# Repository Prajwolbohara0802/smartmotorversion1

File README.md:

# Smart Motors using Arduino

React to this comment or reply here to show your support on this project.

## Components Needed

[Arduino Nano](https://static-01.daraz.com.np/p/9f4c40402cecd5b19b21ea068286c35f.jpg_720x720.jpg_.webp)

[TFT LCD Screen](https://udvabony.com/wp-content/uploads/2019/04/2.4-inch-tft-lcd-shield-for-arduino.jpg)

## Library Needed

Adafruit_GFX.h
Touchscreen.h
Adafruit_TFTLCD.h

[FZP71N4IT58ZZL4.zip](Smart%20Motors%20using%20Arduino%20c2e0098330564f6db3aee58281a698de/FZP71N4IT58ZZL4.zip)

All of these library can be found in Arduino IDE

| TFT pin  | Arduino Pin |
| --- | --- |
| LCD_RD | A0 |
| LCD_WR | A1 |
| LCD_RS | A2 |
| LCD_CS | A3 |
| LCD_RST (optional) | A4 |
| LCD_D0 |  8 |
| LCD_D1 | 9 |
| LCD_D2 | 2 |
| LCD_D3 | 3 |
| LCD_D4 | 4 |
| LCD_D5 | 5 |
| LCD_D6 | 6 |
| LCD_D7 | 7 |
| GND | GND |
| 3.3v  | 3.3 v |
- [x]  

## Pin that are used

| analog device  | Arduino pin |
| --- | --- |
| Sensor | A5 |
|  |  |
|  |  |
- it’s optional to connect Arduino 5v to 5V pin of TFT screen because TFT can easily powerup with the help of 3.3 V
- I prefer connecting the LCD_RST pin of TFT with the RST pin of the Arduino because it left a option to connect the other analog reading device.
- **5V**: Module power supply – 5 V
- **3**.**3V**: Module power supply – 3.3 V
- **GND**: Ground
- **LCD_RST**: LCD bus reset signal, low level reset
- **LCD_CS**: LCD bus chip select signal, low level enable
- **LCD_RS:** LCD bus command / data selection signal, low level: command, high level: data
- **LCD_WR:** LCD bus write signal
- **LCD_RD:** LCD bus read signal
- **LCD_D0:** LCD 8-bit data Bit0
- **LCD_D1:** LCD 8-bit data Bit1
- **LCD_D2:** LCD 8-bit data Bit2
- **LCD_D3:** LCD 8-bit data Bit3
- **LCD_D4:** LCD 8-bit data Bit4
- **LCD_D5:** LCD 8-bit data Bit5
- **LCD_D6:** LCD 8-bit data Bit6
- **LCD_D7:** LCD 8-bit data Bit7

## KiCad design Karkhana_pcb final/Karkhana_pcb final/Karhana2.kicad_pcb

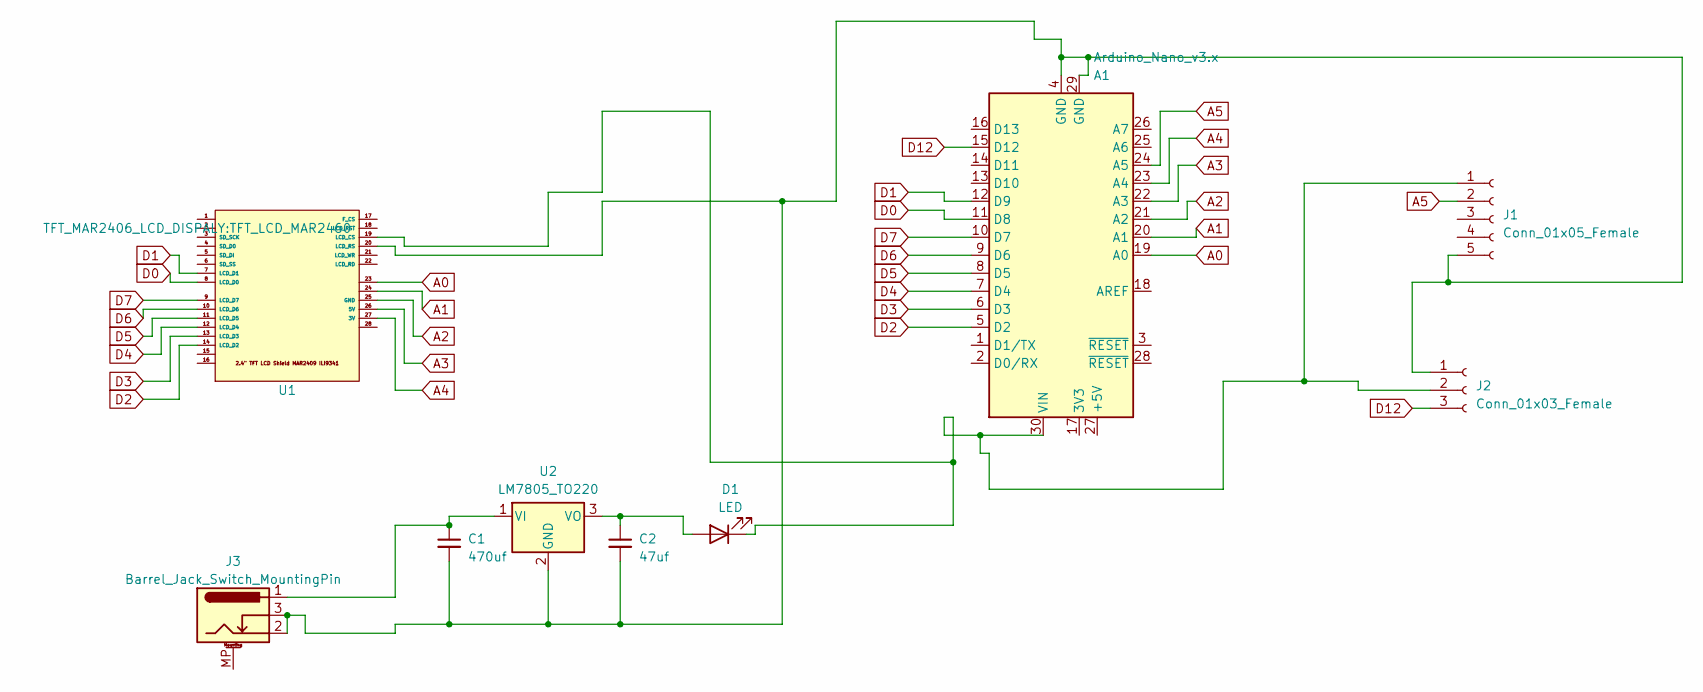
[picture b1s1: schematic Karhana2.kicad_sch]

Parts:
A1: Arduino_Nano_v3.x; Arduino_Nano
C1: 470uf; CP_Elec_5x4.4
C2: 47uf; CP_Elec_5x4.4
D1: LED; CP_Elec_5x4.4
J1: Conn_01x05_Female; PinHeader_1x05_P2.54mm_Vertical_SMD_Pin1Left
J2: Conn_01x03_Female; PinHeader_1x03_P2.54mm_Vertical_SMD_Pin1Left
J3: Barrel_Jack_Switch_MountingPin; BarrelJack_GCT_DCJ200-10-A_Horizontal
U1: TFT_LCD_MAR2460
U2: LM7805_TO220; TO-220-3_Vertical

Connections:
A0: A1.19 (A0), U1.23
A1: A1.20 (A1), U1.24
A2: A1.21 (A2), U1.25 (GND)
A3: A1.22 (A3), U1.26 (5V)
A4: A1.23 (A4), U1.27 (3V)
A5: A1.24 (A5), J1.2
D0: A1.11 (D8), U1.8 (LCD_D0)
D1: A1.12 (D9), U1.7 (LCD_D1)
D2: A1.5 (D2), U1.14 (LCD_D2)
D3: A1.6 (D3), U1.13 (LCD_D3)
D4: A1.7 (D4), U1.12 (LCD_D4)
D5: A1.8 (D5), U1.11 (LCD_D5)
D6: A1.9 (D6), U1.10 (LCD_D6)
D7: A1.10 (D7), U1.9 (LCD_D7)
D12: A1.15 (D12), J2.3
unnamed: A1.4 (GND), A1.29 (GND), C1.2, C2.2, J1.5, J2.1, J3.2, J3.3, U1.20 (LCD_RS), U2.2 (GND)
unnamed: A1.30 (VIN), D1.1 (K), J1.1, J2.2, U1.19 (LCD_CS)
unnamed: C2.1, D1.2 (A), U2.3 (VO)
unnamed: C1.1, J3.1, U2.1 (VI)

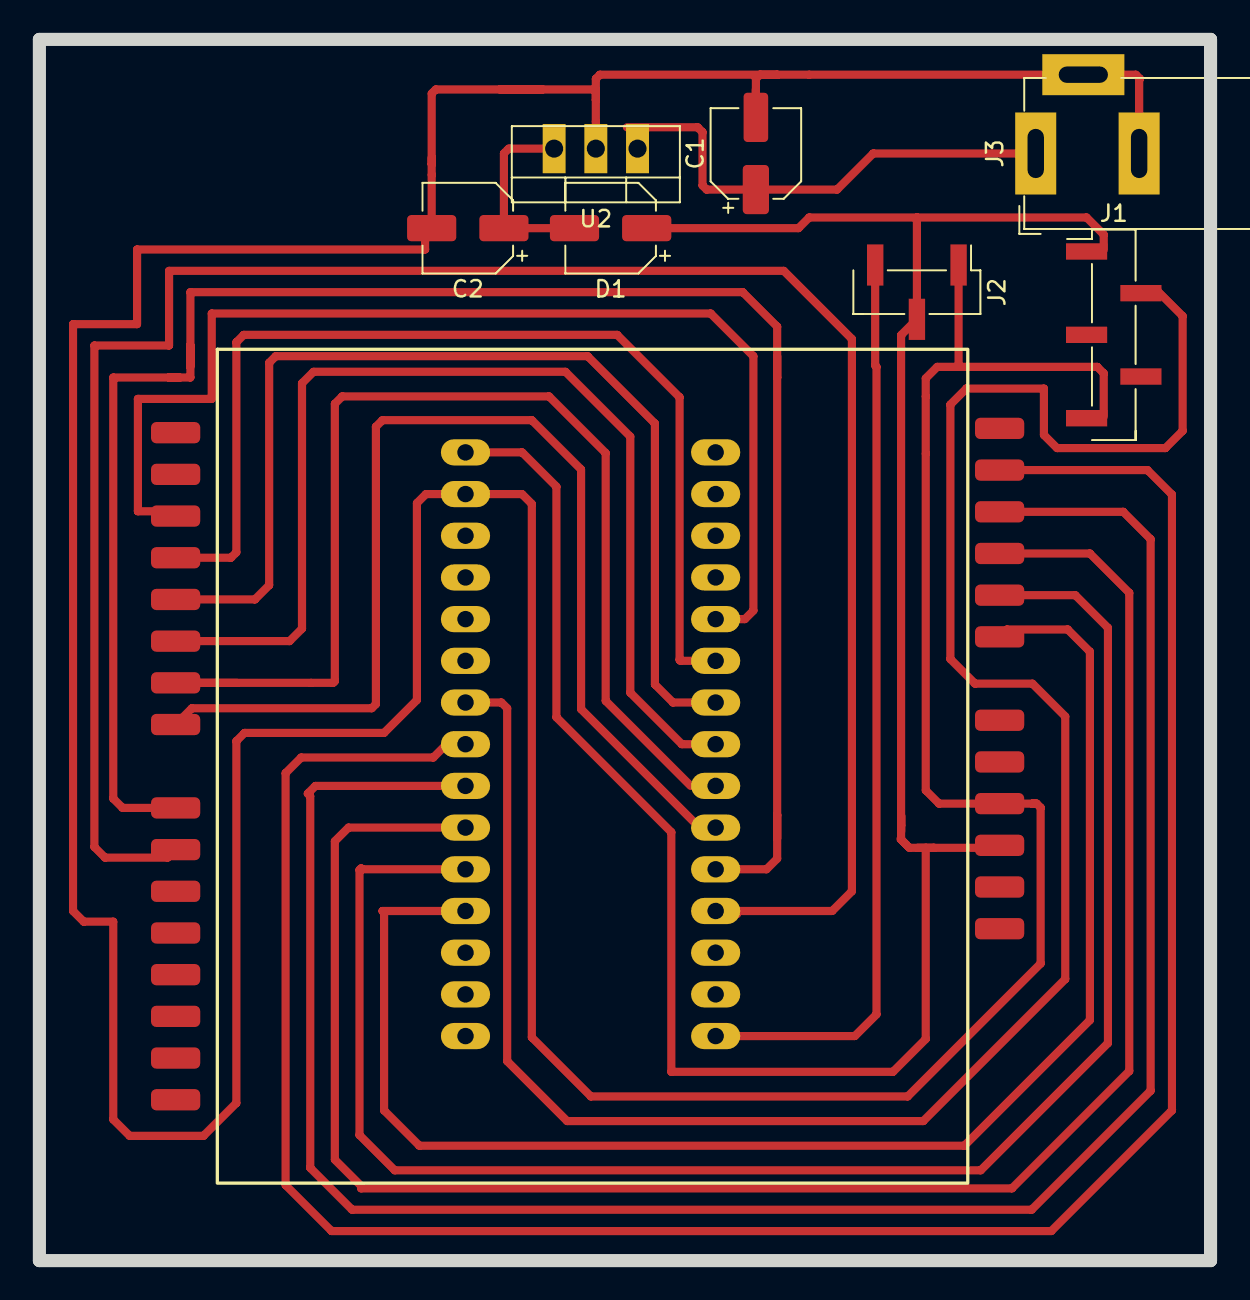
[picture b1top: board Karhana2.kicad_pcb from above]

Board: 2 copper layers, 71.3 x 74.4 mm, 9 parts (1 on the bottom side), 19 nets.

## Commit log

2023-06-19 Initialize main
2023-06-19 Initialize patch-1
2023-06-19 Initialize Prajwolbohara0802-patch-1
2023-06-19 Create Repository description
